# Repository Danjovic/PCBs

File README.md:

# PCBs
PCB sources for several projects

1. SD2IEC - version of board found at https://www.retrohax.net/sd2iec-revisited/

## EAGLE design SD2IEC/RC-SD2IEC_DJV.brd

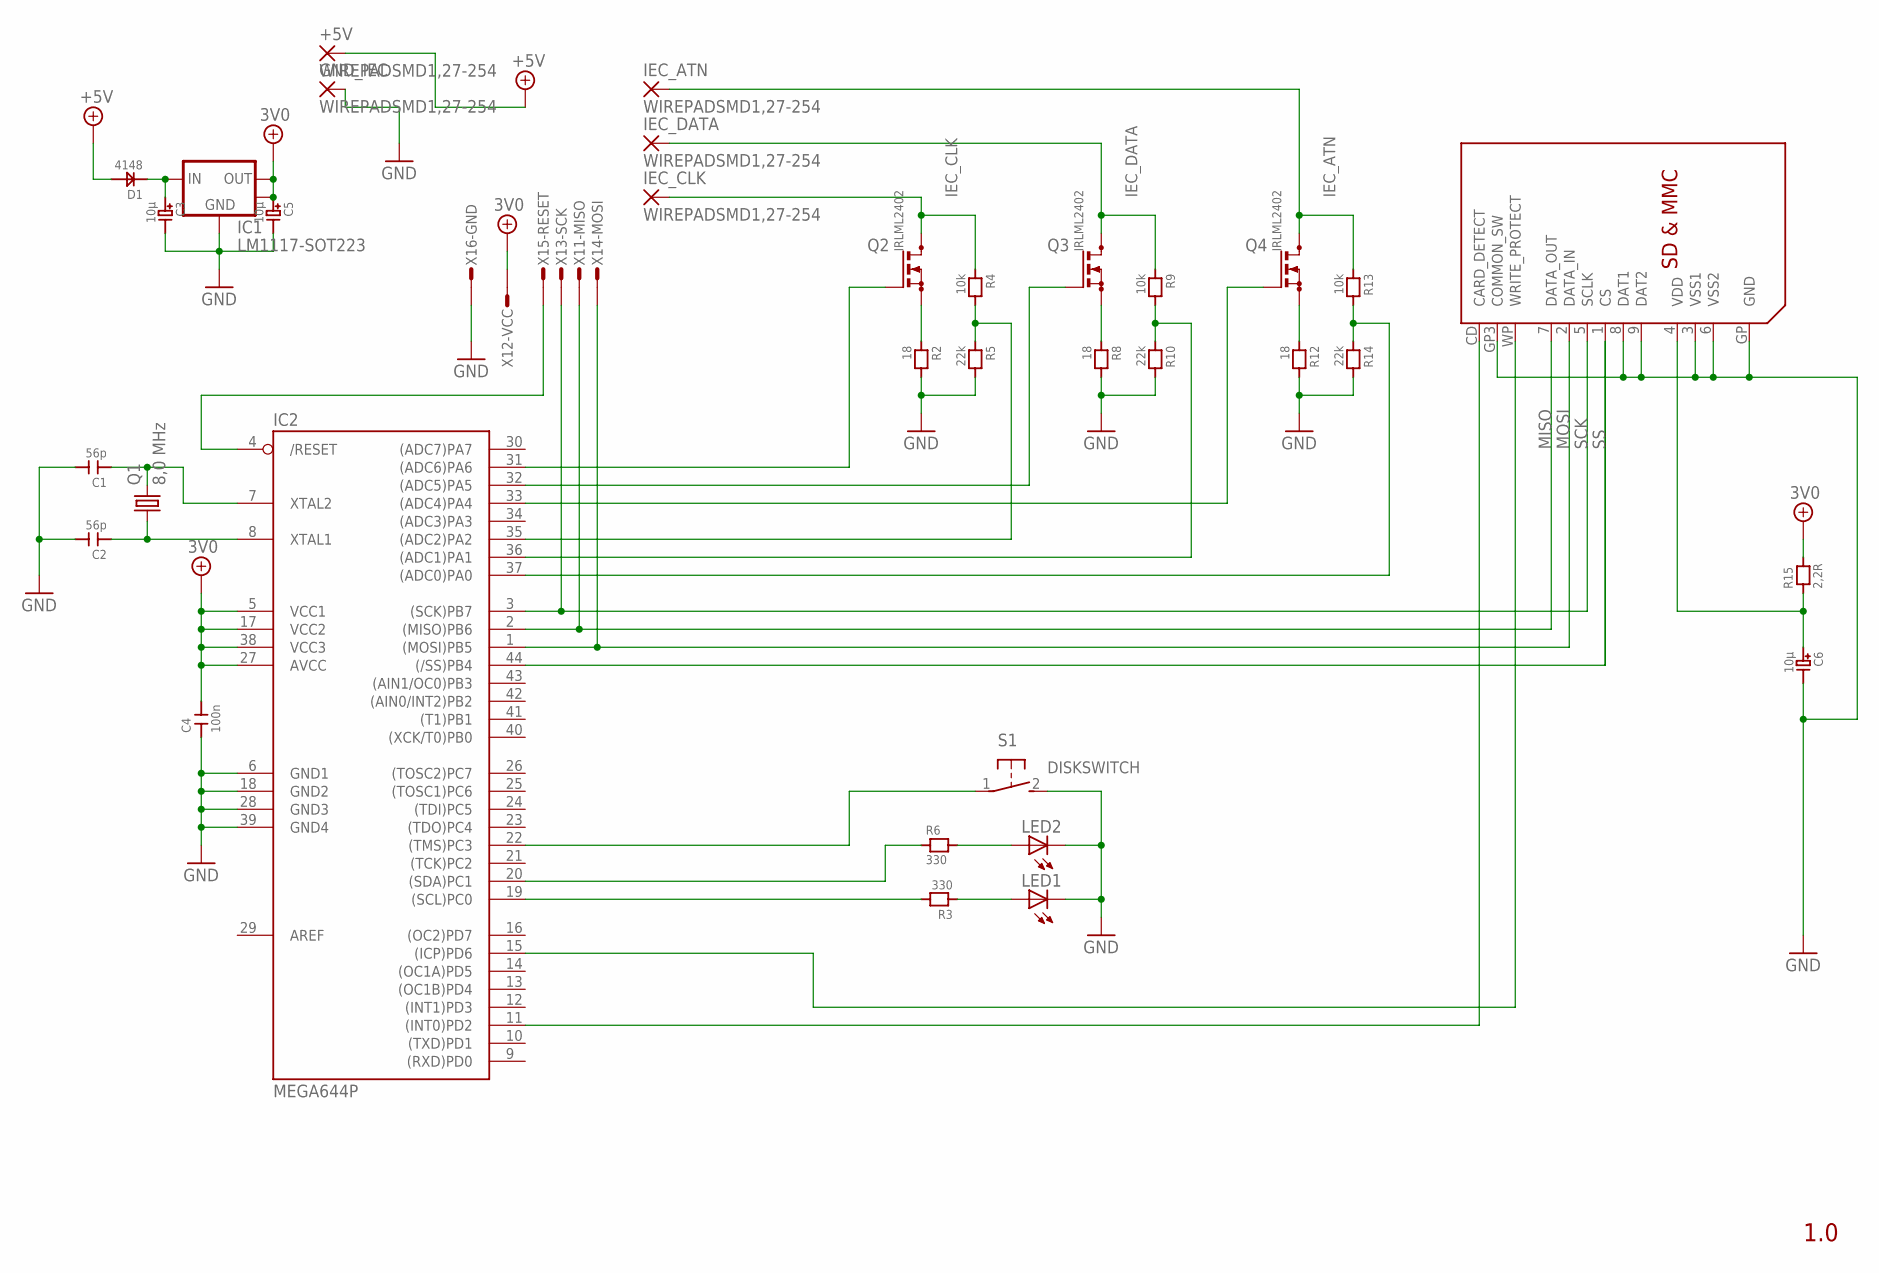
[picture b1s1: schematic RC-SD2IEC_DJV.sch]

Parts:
+5V: WIREPADSMD1,27-254; SMD1,27-2,54
C1, C2: 56p; C0805
C3, C5, C6: 10µ; C_TANTAL_A
C4: 100n; C1206
D1: 4148; SOD-123
GND_IEC: WIREPADSMD1,27-254; SMD1,27-2,54
IC1: LM1117-SOT223; SOT-223-3
IC2: MEGA644P; TQFP44
IEC_ATN: WIREPADSMD1,27-254; SMD1,27-2,54
IEC_CLK: WIREPADSMD1,27-254; SMD1,27-2,54
IEC_DATA: WIREPADSMD1,27-254; SMD1,27-2,54
LED1, LED2: LED3MM
Q1: 8,0 MHz; CTS406
Q2, Q3, Q4: IRLML2402; SOT23_C
R2, R8, R12: 18; R0805
R3, R6: 330; R0805
R4, R9, R13: 10k; R0805
R5, R10, R14: 22k; R0805
R15: 2,2R; R0805
S1: 31-XX; B3F-31XX
SDMMC1: SDMMC06132; 06132
X1: AVR-ISP_1X6; 1X6_ISP

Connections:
3V0: C4.2, C5.1, IC1.2 (VOUT), IC1.4 (HEATSINK), IC2.5 (VCC1), IC2.17 (VCC2), IC2.27 (AVCC), IC2.38 (VCC3), R15.2, X1.2
+5V: +5V.1, D1.2
/RESET: IC2.4 (/RESET), X1.5
ATN: IC2.37 ((ADC0)PA0), R13.2, R14.1
CD: IC2.11 ((INT0)PD2), SDMMC1.CD (CARD_DETECT)
CLK: IC2.35 ((ADC2)PA2), R4.2, R5.1
DATA: IC2.36 ((ADC1)PA1), R9.2, R10.1
DISKSWITCH: IC2.22 ((TMS)PC3), S1.1
GND: C1.2, C2.2, C3.2, C4.1, C5.2, C6.2, GND_IEC.1, IC1.1 (GND), IC2.6 (GND1), IC2.18 (GND2), IC2.28 (GND3), IC2.39 (GND4), LED1.K (C), LED2.K (C), R2.2, R5.2, R8.2, R10.2, R12.2, R14.2, S1.2 (S), SDMMC1.3 (VSS1), SDMMC1.6 (VSS2), SDMMC1.8 (DAT1), SDMMC1.9 (DAT2), SDMMC1.GP (GND), SDMMC1.GP3 (COMMON_SW), X1.6
IEC_ATN: IEC_ATN.1, Q4.3 (D), R13.1
IEC_CLK: IEC_CLK.1, Q2.3 (D), R4.1
IEC_DATA: IEC_DATA.1, Q3.3 (D), R9.1
LED1: LED2.A, R6.2
LED2: LED1.A, R3.1
MISO: IC2.2 ((MISO)PB6), SDMMC1.7 (DATA_OUT), X1.1
MOSI: IC2.1 ((MOSI)PB5), SDMMC1.2 (DATA_IN), X1.4
unnamed: C3.1, D1.1, IC1.3 (VIN)
unnamed: C2.1, IC2.8 (XTAL1), Q1.1
unnamed: C1.1, IC2.7 (XTAL2), Q1.3 (2)
unnamed: IC2.32 ((ADC5)PA5), Q3.1 (G)
unnamed: IC2.33 ((ADC4)PA4), Q4.1 (G)
unnamed: IC2.31 ((ADC6)PA6), Q2.1 (G)
unnamed: Q2.2 (S), R2.1
unnamed: Q3.2 (S), R8.1
unnamed: Q4.2 (S), R12.1
PC0: IC2.19 ((SCL)PC0), R3.2
PC1: IC2.20 ((SDA)PC1), R6.1
SCK: IC2.3 ((SCK)PB7), SDMMC1.5 (SCLK), X1.3
SS: IC2.44 ((/SS)PB4), SDMMC1.1 (CS)
VDD: C6.1, R15.1, SDMMC1.4 (VDD)
WP: IC2.15 ((ICP)PD6), SDMMC1.WP (WRITE_PROTECT)

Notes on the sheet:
1.0

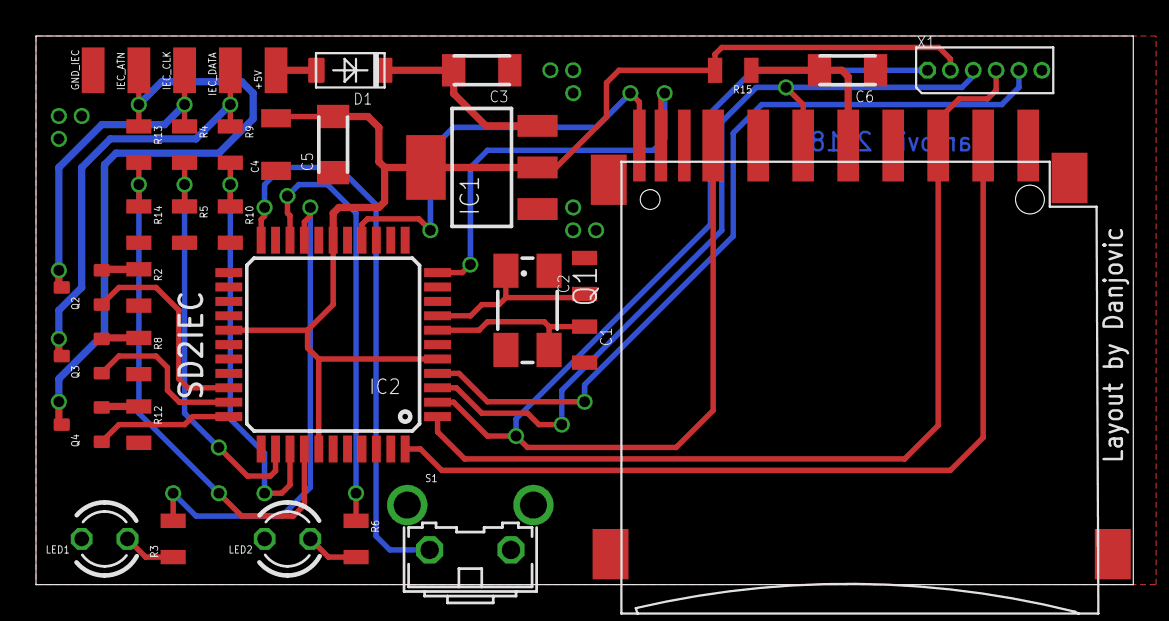
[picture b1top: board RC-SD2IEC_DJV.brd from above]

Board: 2 copper layers, 61.0 x 30.5 mm, 35 parts (0 on the bottom side), 31 nets.

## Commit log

2018-06-12 My version of SD2IEC revisited
    Original project: https://oshpark.com/shared_projects/xKYne70v
2018-12-13 Adicionadas medidas placas CP200s
